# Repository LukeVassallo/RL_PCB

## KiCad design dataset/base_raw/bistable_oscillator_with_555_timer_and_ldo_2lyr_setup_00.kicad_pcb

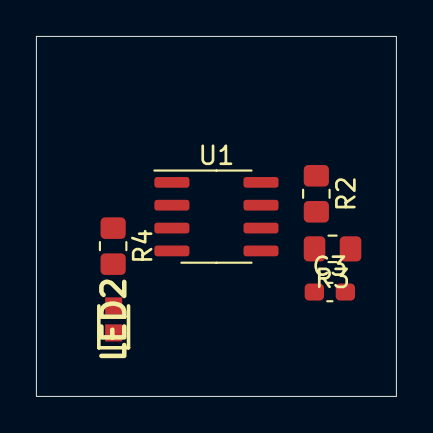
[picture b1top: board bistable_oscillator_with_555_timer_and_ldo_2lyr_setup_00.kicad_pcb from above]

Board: 2 copper layers, 20.0 x 20.0 mm, 6 parts (0 on the bottom side), 6 nets, no tracks yet.

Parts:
C3: 1uF; C_0603_1608Metric_Pad1.08x0.95mm_HandSolder
LED2: 150060VS75000; LEDC1608X80N
R2: 47k; R_0805_2012Metric_Pad1.20x1.40mm_HandSolder
R3: 120k; R_0805_2012Metric_Pad1.20x1.40mm_HandSolder
R4: 2k; R_0805_2012Metric_Pad1.20x1.40mm_HandSolder
U1: NE555D; SOIC-8_3.9x4.9mm_P1.27mm

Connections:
+3V3: R2.1, U1.4, U1.8
GND: C3.2, LED2.1, U1.1
unnamed: C3.1, R3.2, U1.2, U1.6
unnamed: LED2.2, R4.2
unnamed: R2.2, R3.1, U1.7
unnamed: R4.1, U1.3
